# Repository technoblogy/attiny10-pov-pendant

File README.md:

# ATtiny10 POV Pendant
A miniature pendant based on the ATtiny10 that produces coloured stripes when you move.
For more information see http://www.technoblogy.com/show?201J.

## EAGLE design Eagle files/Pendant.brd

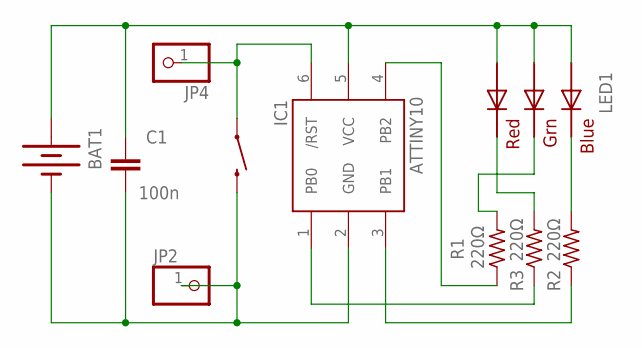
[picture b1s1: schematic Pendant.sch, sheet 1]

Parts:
BAT1: BATTERY12MM; BATTCON_12MM
C1: 100n; 0603-CAP
IC1: ATTINY10; SOT23-6
JP2, JP4: PINHD-1X1CB; 1X01-CLEANBIG
LED1: RGBLED5050
R1, R2, R3: 220Ω; R0805
S2: SWITCH-MOMENTARY-2SMD; TACTILE-SWITCH-SMD

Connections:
unnamed: BAT1.PWR@1 (+), C1.1, IC1.5 (VCC), LED1.1 (GREEN_A), LED1.2 (RED_A), LED1.3 (BLUE_A)
unnamed: IC1.6 (/RST), JP4.1, S2.1
unnamed: LED1.5 (RED_C), R3.2
unnamed: LED1.6 (GREEN_C), R1.2
unnamed: LED1.4 (BLUE_C), R2.2
unnamed: IC1.1 (PB0), R3.1
unnamed: BAT1.GND (-), C1.2, IC1.2 (GND), JP2.1, S2.3 (2)
unnamed: IC1.3 (PB1), R2.1
unnamed: IC1.4 (PB2), R1.1

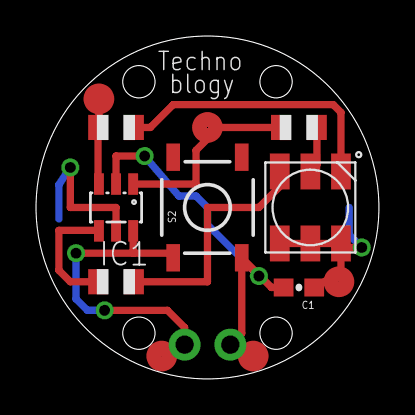
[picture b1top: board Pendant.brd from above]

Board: 2 copper layers, 19.1 x 19.1 mm, 10 parts (1 on the bottom side), 9 nets.

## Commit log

2018-05-19 Version 1 - 19th May 2018
2018-05-19 Veraion 1 - 19th May 2018
2018-08-04 Gerber files
2021-03-07 Version 2 - 7th March 2021

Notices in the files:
parts and their libraries:
SparkFun-Capacitors: Licensing: CC v3.0 Share-Alike You are welcome to use this library for commercial purposes.
SparkFun-Electromechanical: Licensing: Creative Commons ShareAlike 4.0 International - https://creativecommons.org/licenses/by-sa/4.0
